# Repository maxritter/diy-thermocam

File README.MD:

# DIY-Thermocam

The DIY-Thermocam V3 is an open-source thermal imager based on the FLIR Lepton LWIR sensor.

Check out the official website for more information about the project: **[www.diy-thermocam.net](https://www.diy-thermocam.net/)**

**This repository contains:**

- **[Latest firmware releases](https://github.com/maxritter/diy-thermocam/releases)**
- **[Open-source firmware](https://github.com/maxritter/diy-thermocam/tree/master/firmware)**
- **[Desktop software](https://github.com/maxritter/diy-thermocam/tree/master/software)** 
- **[Device enclosure](https://github.com/maxritter/diy-thermocam/tree/master/enclosure)**
- **[Printed circuit board](https://github.com/maxritter/diy-thermocam/tree/master/pcb)**

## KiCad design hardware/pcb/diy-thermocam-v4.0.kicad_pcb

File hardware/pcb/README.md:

# DIY-Thermocam V4.0 PCB

The main board of the camera. A PCB manufacturer makes it and solders all parts on. You then plug in the Teensy 4.1, the FLIR Lepton on its Breakout Board V2.0, the display and the battery.

| Display side (top) | Module side (bottom) |
| --- | --- |
|  |  |

## Order the board

Choose a manufacturer and upload the three files from that manufacturer's folder in [`fab/`](fab/):

- the Gerber zip, `diy-thermocam-v4.0-bom.csv` and `diy-thermocam-v4.0-cpl.csv`

| Manufacturer | Folder | Good to know |
| --- | --- | --- |
| **[JLCPCB](https://jlcpcb.com/)** (recommended) | [`fab/jlcpcb/`](fab/jlcpcb/) | The Gerber zip is `diy-thermocam-v4.0-panel-gerbers.zip`: the board sits in its own routed break-off frame (see below). Every part comes from JLCPCB's own stock. The boost converter `U2` (`C2071784`) runs low at times; if the order shows a shortfall, pre-order it in the parts manager. Assembly starts at 2 boards. |
| [Seeed Fusion](https://www.seeedstudio.com/fusion_pcb.html) | [`fab/seeed/`](fab/seeed/) | Upload `diy-thermocam-v4.0-gerbers.zip`. Seeed buys the parts; the BOM links each one on LCSC. Also upload both assembly drawings. Takes about 4 weeks. |
| [PCBWay](https://www.pcbway.com/pcb-assembly.html) | [`fab/pcbway/`](fab/pcbway/) | Upload `diy-thermocam-v4.0-gerbers.zip`. PCBWay buys the parts; the notes column lists each LCSC number. Answer "no" to Chinese substitutes. |

**Board options:** 2 layers, 89.4 × 68.4 mm, 1.6 mm FR-4, 1 oz copper, lead-free HASL or ENIG, any solder mask colour.

**Assembly:** no soldering iron needed. Order double-sided assembly (Standard PCBA at JLCPCB), because the board has a part on its top side: all SMD parts and the Teensy and Lepton sockets go on the bottom side; only the display socket `J1` (2×20, through-hole) sits on the top side.

**Panel at JLCPCB.** Double-sided assembly needs a board of at least 70 × 70 mm. The JLCPCB Gerber already holds the board in a 107.4 × 86.4 mm routed frame with small break-off tabs, three tooling holes and six fiducials. The tabs stay clear of the USB-C connector, both switches and the tripod fin. In the order form:

- choose *Delivery Format: Panel by Customer*, 1 design, 1 × 1, and add no edge rails: the frame is in the file;
- in the assembly options set *Tooling holes: Added by Customer*, because the frame already has them;
- keep the CPL file as it is: its coordinates match the board inside the frame;
- turn on production-file confirmation, so you approve the placement before assembly starts;
- add the remark *"Seat the through-hole sockets (J1, J2, J5, J6) flush and square before soldering."*

Standard PCBA adds a setup fee, a stencil and a hand-soldering charge for the through-hole parts; the quote shows them before you pay. The boards arrive in their frames. Snap each one out by bending the frame, never the board, and never lever against the USB-C connector or the switches. File the small tab stubs flush.

**Before you confirm the production files,** compare the bottom placement with [`fab/diy-thermocam-v4.0-assembly-bottom.pdf`](fab/diy-thermocam-v4.0-assembly-bottom.pdf). The pin-1 marks of `U2`, `U3`, `U4`, `D1`, `D2`, `Q1` and `Q2` must line up. Rotations of bottom-side parts are the most common assembly mistake.

**Do not substitute** these parts; their heights, footprints or timing are part of the design:

- the spring pins `P1`–`P4`, the sockets `J1`, `J2`, `J5` and `J6`, the USB-C connector `J3` and the inductor `L1`.

## What you plug in

- **Teensy 4.1 with pins** into `J5`/`J6`, as it comes. Leave its five inner pads empty: spring pins `P3` (`VBAT`, clock supply) and `P4` (`Program`, PROG button) press on them from below. If pins are soldered there, cut them flush underneath first; never force the Teensy down.
- **FLIR Lepton 3.5** (or 3.1R or 2.5) snapped into a **FLIR Lepton Breakout Board V2.0 (`250-0577-00`, Rev R200)**, fitted onto a **Sullins `PPPC102LJBN-RC`** right-angle 2×10 female header (3.15 mm tails; do not substitute shorter-tail headers). Check the breakout label on arrival: older Rev R120 boards had D1 fitted backwards and cannot power from `J2` pin 2. Mount the breakout on four M2×18 screws with 12 mm sleeves plus three 0.3 mm M2 nylon washers (`003.03.010`) on each sleeve (= 12.9 mm spacing) and 1.2 mm ISO 4035 M2 thin nuts (`002.09.012`), so the right-angle header's bends clear `J2` even at worst-case socket height (+0.24 mm) while its legs seat 3.8 mm deep into `J2`.
- **BuyDisplay `ER-TFTM032-3`** into `J1`, from the display side.
- **LiPo battery** (Adafruit 258, or a `505060` cell; JST-PH) into `J4`. Check that its `+` wire matches the `+` mark first.

The full parts list with shops is in [`hardware/bom/`](../bom/README.md).

## What is on the board

| Function | How it works |
| --- | --- |
| USB-C | Charges the battery and carries USB data. Two spring pins (`P1`, `P2`) press on the USB pads under the Teensy, so the Teensy's own micro-USB port stays unused. Never plug a cable into it while the board is powered. |
| Charging | TI BQ24074 powers the camera over USB while charging the battery (about 0.45 A charge current via `R10 = 2.0 kΩ`, strictly under Adafruit 258's 500 mA limit; red `CHG` LED). Its USB input limit is 1.3 A nominal (up to 1.45 A worst case), so use a charger or port rated 1.5 A or more; a 500 mA hub port can cut out. |
| 5 V supply | TI TPS61022 boost converter. The slide switch `SW1` turns the camera off; the battery still charges while it is off. |
| Battery protection | `Q1`/`Q2` block a battery plugged in the wrong way round; `F1` is a 2 A resettable fuse. |
| Clock | An XC6206 regulator keeps the Teensy's clock running from the battery through spring pin `P3`, so no coin cell is needed. |
| Buttons | `SW2` capture button at the board edge; `SW3` PROG button behind a pinhole for firmware recovery, wired to the Teensy through spring pin `P4`. |
| Touch | Resistive touch works as delivered. A capacitive-touch display needs a soldering iron: cut `JP1`/`JP2` between pads 1–2, bridge pads 2–3, and close `JP3`. |

## First power-up

1. Main board only, battery connected, `SW1` on: 5.0 V (4.9–5.1 V) between `VIN` and `GND` on the Teensy socket. `SW1` off: 0 V.
2. Plug in USB-C: the red `CHG` LED lights while the battery charges.
3. With the Teensy plugged in, connect USB-C to a computer: the Teensy shows up as a USB device. This confirms `P1`/`P2` touch its USB pads.
4. Press PROG through the pinhole: Teensy Loader shows the Teensy in bootloader mode. This confirms `P4`.
5. Set the clock, switch off with `SW1` for a minute and on again: the time kept running. This confirms `P3`.
6. Plug in the FLIR Lepton Breakout Board V2.0 (with the Lepton snapped in) via the right-angle 2×10 female header into `J2`, switch on: the live thermal image appears.

## Change the design

The KiCad 10 project is [`diy-thermocam-v4.0`](diy-thermocam-v4.0.kicad_sch) with its symbol and footprint libraries ([`V40.kicad_sym`](V40.kicad_sym), [`V40.pretty/`](V40.pretty/), [`V40.3dshapes/`](V40.3dshapes/)). Part numbers live in [`hardware/bom/bom.csv`](../bom/bom.csv).

After a change, check the board and rebuild the order files:

```bash
kicad-cli sch erc --severity-error --exit-code-violations hardware/pcb/diy-thermocam-v4.0.kicad_sch
kicad-cli pcb drc --refill-zones --schematic-parity --severity-error --exit-code-violations hardware/pcb/diy-thermocam-v4.0.kicad_pcb
python3 hardware/pcb/scripts/export_fab.py
```

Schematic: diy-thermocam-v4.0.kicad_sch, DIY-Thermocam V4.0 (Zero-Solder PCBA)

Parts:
C1, C2, C3, C5, C10: 10uF; C_0805
C4, C8, C9: 22uF; C_0805
C6, C7, C11, C12: 100nF; C_0603
D1: USBLC6-2SC6; SOT23_6
D2: LED_Red_CHG; LED_0603
F1: PTC_2A_1206; FUSE_1206
H1, H2, H3, H4: M2.5_Hole; MountingHole_2.8mm_M2.5_Pad
J1: Display_2x20_Socket; PinSocket_2x20_Display
J2: Lepton_2x10_Socket; PinSocket_2x10_Lepton
J3: TYPE-C-31-M-12; USB_C_TYPE_C_31_M_12
J4: S2B-PH-SM4-TB; JST_PH_2P_RA
J5: Teensy_1x24_L; PinSocket_1x24
J6: Teensy_1x24_R; PinSocket_1x24
J8: I2C_EXT_DNP; I2C_PADS_1x04
JP1: CTP_SCL_SEL; SJ_3P_BRIDGED12
JP2: CTP_SDA_SEL; SJ_3P_BRIDGED12
JP3: CTP_INT_OPT; SJ_2P_OPEN
L1: 1.0uH_15A; L_0630
P1: Pogo_USB_DP; PogoPin_SMD_2.0mm
P2: Pogo_USB_DM; PogoPin_SMD_2.0mm
P3: Pogo_Teensy_VBAT; PogoPin_SMD_2.0mm
P4: Pogo_Teensy_PROG; PogoPin_SMD_2.0mm
Q1: AO3401A_RevPol; SOT23
Q2: AO3400A_RevPol_Ctl; SOT23
R1: 470k; R_0603
R2: 1M; R_0603
R3, R5, R15, R17, R24: 100k; R_0603
R4, R6: 4.7k; R_0603
R7, R8: 5.1k; R_0603
R9, R22: 10k; R_0603
R10: 2.0k; R_0603
R11: 1.2k; R_0603
R12: 1.0k; R_0603
R14, R20: 47k; R_0603
R16: 732k; R_0603
R18, R21: 750k; R_0603
R19: 10k_BL_PU; R_0603
R23: 3.0k; R_0603
SW1: JS102011SAQN; SW_SLIDE_RA
SW2: B3U-3000P; SW_TACT_RA
SW3: TS-1187A; SW_TACT_PROG
U2: TPS61022RWUT; TPS61022_VQFN7
U3: BQ24074RGTR; BQ24074_VQFN16
U4: XC6206P332MR_RTC; SOT23

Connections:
3V3: C7.1, J1.21, J5.15, J6.3, J8.2, R4.1, R6.1, R19.2, SW2.1
5V: C4.1, C5.1, C6.1, C9.1, J1.2, J2.2, J6.1, R16.1, U2.3
A16: J6.17, R3.2, R5.1
BOOST_EN: R15.1, SW1.2, U2.5
BOOST_FB: R16.2, R17.1, U2.4
BOOST_SW: L1.2, U2.2
BQ_CHG_N: D2.1, U3.9
BQ_EN2: R22.2, U3.5
BQ_ILIM: R11.1, U3.12
BQ_ISET: R10.1, U3.16
BQ_ITERM: R23.1, U3.15
BQ_TMR: R14.1, U3.14
BQ_TS: R9.1, U3.1
CTP_INT: J1.39, JP3.1
D2: J5.4, SW2.2
D3: J2.15, J5.5
D4: J5.6, JP3.2
D5: J5.7, JP2.1
D9: J5.11, JP1.1
D10: J1.25, J5.12
D11: J1.27, J1.34, J5.13
D12: J1.28, J1.32, J5.14
D13: J1.24, J1.33, J6.14
D18: J2.5, J6.9, J8.3, JP2.3, R4.2
D19: J2.8, J6.8, J8.4, JP1.3, R6.2
D21: J1.23, J6.6
D22: J1.29, J6.5, R19.1
D23: C12.1, J6.4, R1.2, R2.1
D26: J2.9, J5.18
D27: J2.7, J5.19
D38: J2.10, J6.19
D39: J2.12, J6.18
GND: C1.2, C2.2, C3.2, C4.2, C5.2, C6.2, C7.2, C8.2, C9.2, C10.2, C11.2, C12.2, D1.2, H1.1, H2.1, H3.1, H4.1, J1.1, J1.40, J2.1, J2.19, J3.A1, J3.A12, J3.B1, J3.B12, J3.SH, J4.2, J4.MP, J5.1, J6.2, J6.15, J8.1, Q2.2, R2.2, R5.2, R7.2, R8.2, R9.2, R10.2, R11.2, R14.2, R15.2, R17.2, R21.2, R23.2, SW1.1, SW3.1, U2.1, U2.6, U3.4, U3.6, U3.8, U3.17, U4.1
LCD_P30: J1.30, JP1.2
LCD_P31: J1.31, JP2.2
LED_CHG_A: D2.2, R12.2
LIPO_PROT: F1.1, Q1.2, R18.2, R24.1
LIPO_RAW: J4.1, Q1.3, R20.1, R24.2
Q1_GATE: Q1.1, Q2.3, R18.1
Q2_GATE: Q2.1, R20.2, R21.1
TEENSY_PROG: P4.1, SW3.2
USB_CC1: J3.A5, R7.1
USB_CC2: J3.B5, R8.1
USB_DM_RAW: D1.1, D1.6, J3.A7, J3.B7, P2.1
USB_DP_RAW: D1.3, D1.4, J3.A6, J3.B6, P1.1
VBAT: C10.1, P3.1, U4.2
VBUS: C1.1, D1.5, J3.A4, J3.A9, J3.B4, J3.B9, R3.1, R12.1, U3.13
VLIPO: C3.1, C11.1, F1.2, R1.1, U3.2, U3.3, U4.3
VSYS: C2.1, C8.1, L1.1, R22.1, SW1.3, U2.7, U3.10, U3.11

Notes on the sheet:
Switches, LEDs, JST-PH LiPo & Sensing
Teensy 4.1 Sockets + Zero-Solder USB Pogo Pins
3.2-inch Display & FLIR Lepton Sockets
TI TPS61022 5V Synchronous Boost + Decoupling
DIY-Thermocam V4.0 (Zero-Solder PCBA)
TI BQ24074 Power-Path Charger
USB-C + ESD

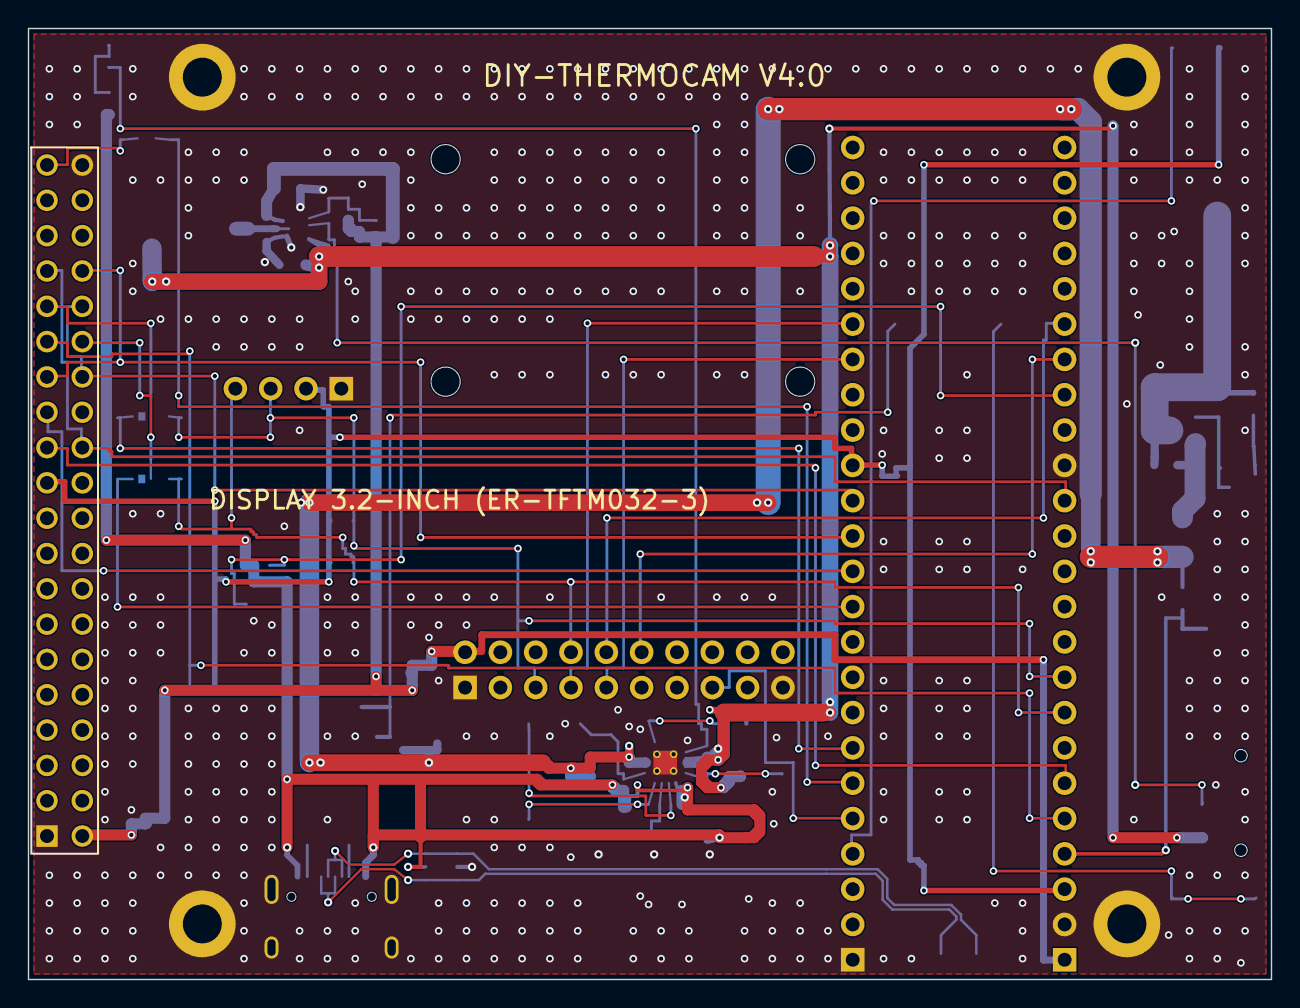
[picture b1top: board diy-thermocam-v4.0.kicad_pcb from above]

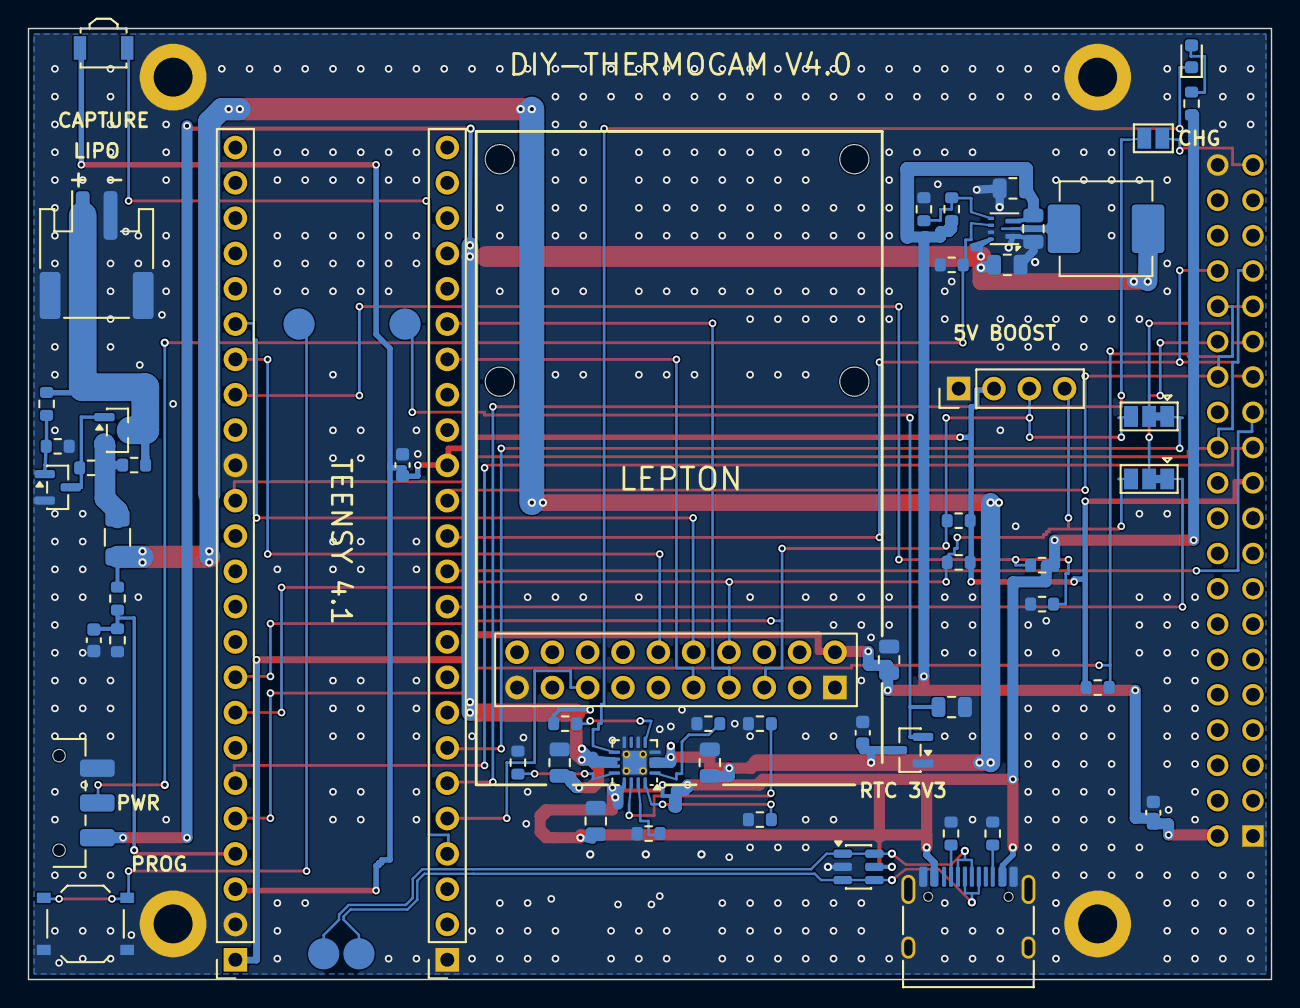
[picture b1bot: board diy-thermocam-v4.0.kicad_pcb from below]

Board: 2 copper layers, 89.4 x 68.4 mm, 69 parts (60 on the bottom side), 49 nets.

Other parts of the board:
H5, H6, H7, H8: M2_Lepton; MountingHole_2.1mm_M2

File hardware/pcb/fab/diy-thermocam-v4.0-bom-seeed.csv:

Designator,MPN,Qty,Seeed OPL,LCSC,Value,Footprint,Mount,PCBA Tier
"C1,C10,C2,C3,C5",CL21A106KAYNNNE,5,,C15850,10uF,C_0805,SMD,basic
"C11,C6,C7",CC0603KRX7R9BB104,3,,C14663,100nF,C_0603,SMD,basic
"C4,C8,C9",CL21A226MAQNNNE,3,,C45783,22uF,C_0805,SMD,basic
D1,USBLC6-2SC6,1,,C7519,USBLC6-2SC6,SOT23_6,SMD,extended
D2,KT-0603R,1,,C2286,LED_Red_CHG,LED_0603,SMD,basic
F1,SMD1206P200TF,1,,C20988,PTC_2A_1206,FUSE_1206,SMD,extended
J1,2.54-2*20,1,,C2977589,Display_2x20_Socket,PinSocket_2x20_Display,THT,extended
J2,DS1023-02-2x10SF11,1,,C18164970,Lepton_2x10_Socket,PinSocket_2x10_Lepton,THT,extended
J3,TYPE-C-31-M-12,1,,C165948,TYPE-C-31-M-12,USB_C_TYPE_C_31_M_12,SMD,extended
J4,S2B-PH-SM4-TB(LF)(SN),1,,C295747,S2B-PH-SM4-TB,JST_PH_2P_RA,SMD,extended
J5,HC-PM254-8.5H-1x24PZ,1,,C41376163,Teensy_1x24_L,PinSocket_1x24,THT,extended
J6,HC-PM254-8.5H-1x24PZ,1,,C41376163,Teensy_1x24_R,PinSocket_1x24,THT,extended
J7,2.54-1*5PFemale,1,,C50950,Teensy_1x05_Inner,PinSocket_1x05,THT,extended
L1,FXL0630-1R0-M,1,,C167216,1.0uH_15A,L_0630,SMD,extended
P1,YTC1P-8535-01,1,,C5221289,Pogo_USB_DP,PogoPin_SMD_2.0mm,SMD,extended
P2,YTC1P-8535-01,1,,C5221289,Pogo_USB_DM,PogoPin_SMD_2.0mm,SMD,extended
Q1,AO3401A,1,,C15127,AO3401A_RevPol,SOT23,SMD,basic
Q2,AO3400A,1,,C20917,AO3400A_RevPol_Ctl,SOT23,SMD,basic
"R1,R14,R20",0603WAF4702T5E,3,,C25819,47k,R_0603,SMD,basic
"R10,R12",0603WAF1001T5E,2,,C21190,1.0k,R_0603,SMD,basic
R11,0603WAF1201T5E,1,,C22765,1.2k,R_0603,SMD,basic
"R15,R17,R2,R3,R5",0603WAF1003T5E,5,,C25803,100k,R_0603,SMD,basic
"R16,R18,R21",0603WAF7503T5E,3,,C23240,750k,R_0603,SMD,extended
R19,0603WAF1002T5E,1,,C25804,10k_BL_PU,R_0603,SMD,basic
"R22,R9",0603WAF1002T5E,2,,C25804,10k,R_0603,SMD,basic
R23,0603WAF3001T5E,1,,C4211,3.0k,R_0603,SMD,basic
"R4,R6",0603WAF4701T5E,2,,C23162,4.7k,R_0603,SMD,basic
"R7,R8",0603WAF5101T5E,2,,C23186,5.1k,R_0603,SMD,basic
SW1,JS102011SAQN,1,,C221660,JS102011SAQN,SW_SLIDE_RA,SMD,extended
SW2,B3U-3000P,1,,C963349,B3U-3000P,SW_TACT_RA,SMD,extended
SW3,TS-1187A-B-A-B,1,,C318884,TS-1187A,SW_TACT_PROG,SMD,basic
U2,TPS61022RWUR,1,,C915088,TPS61022RWUR,TPS61022_VQFN7,SMD,extended
U3,BQ24074RGTR,1,,C54313,BQ24074RGTR,BQ24075_VQFN16,SMD,extended
U4,XC6206P332MR-G,1,,C5446,XC6206P332MR_RTC,SOT23,SMD,basic

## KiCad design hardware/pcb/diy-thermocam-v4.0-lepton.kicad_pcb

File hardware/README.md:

# DIY-Thermocam Hardware

PCB, enclosure, and Bill of Materials files for DIY-Thermocam, licensed under [CC BY-NC-SA 4.0](LICENSE): free to build and change for non-commercial use.

- **[PCB (`pcb/`)](pcb/README.md)** — KiCad 10 sources for the V4.0 main board (fully assembled by the fab), with Gerbers, BOM/CPL exports and 3D STEP models (`pcb/fab/`).
- **[Enclosure (`enclosure/`)](enclosure/README.md)** — Parametric [build123d](https://github.com/gumyr/build123d) CAD (`enclosure/cad/`), 3D-printed and laser-cut exports (`enclosure/exports/`), and Blender renders (`enclosure/renders/`).
- **[Bill of Materials (`bom/`)](bom/README.md)** — Single-source `bom.csv`, schema validator, and order guide.

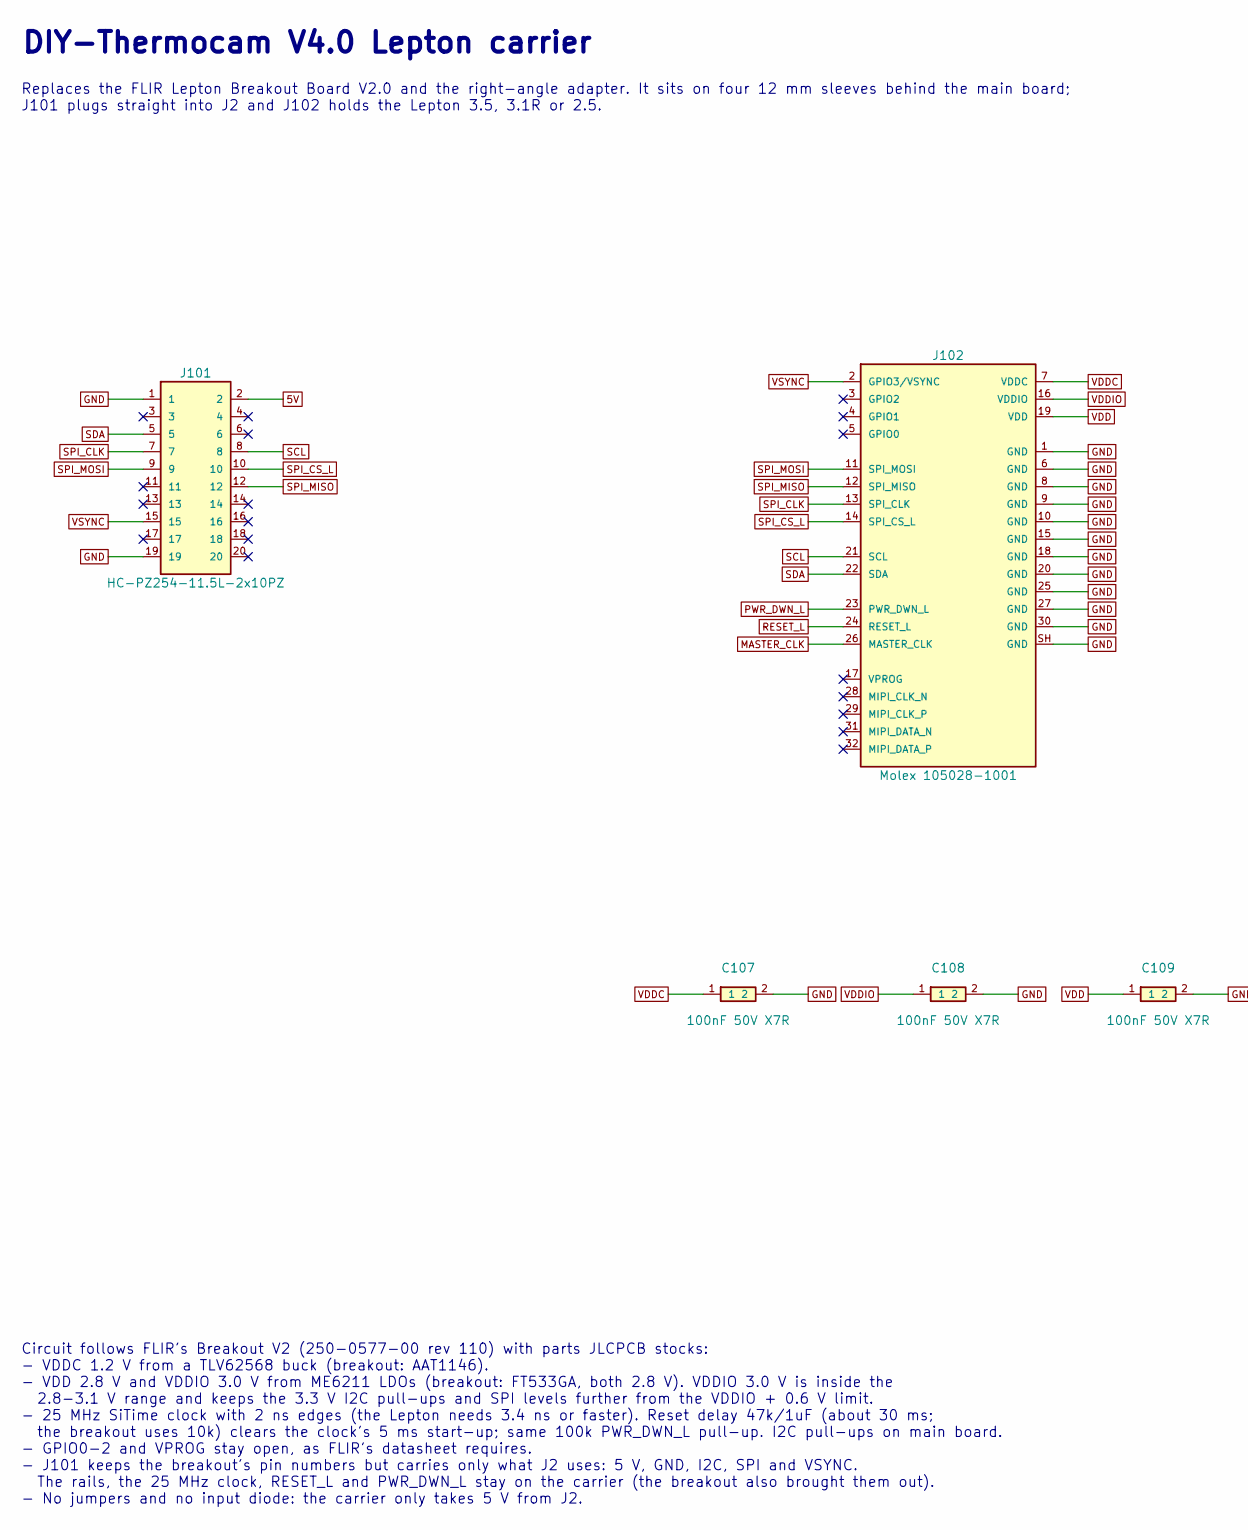
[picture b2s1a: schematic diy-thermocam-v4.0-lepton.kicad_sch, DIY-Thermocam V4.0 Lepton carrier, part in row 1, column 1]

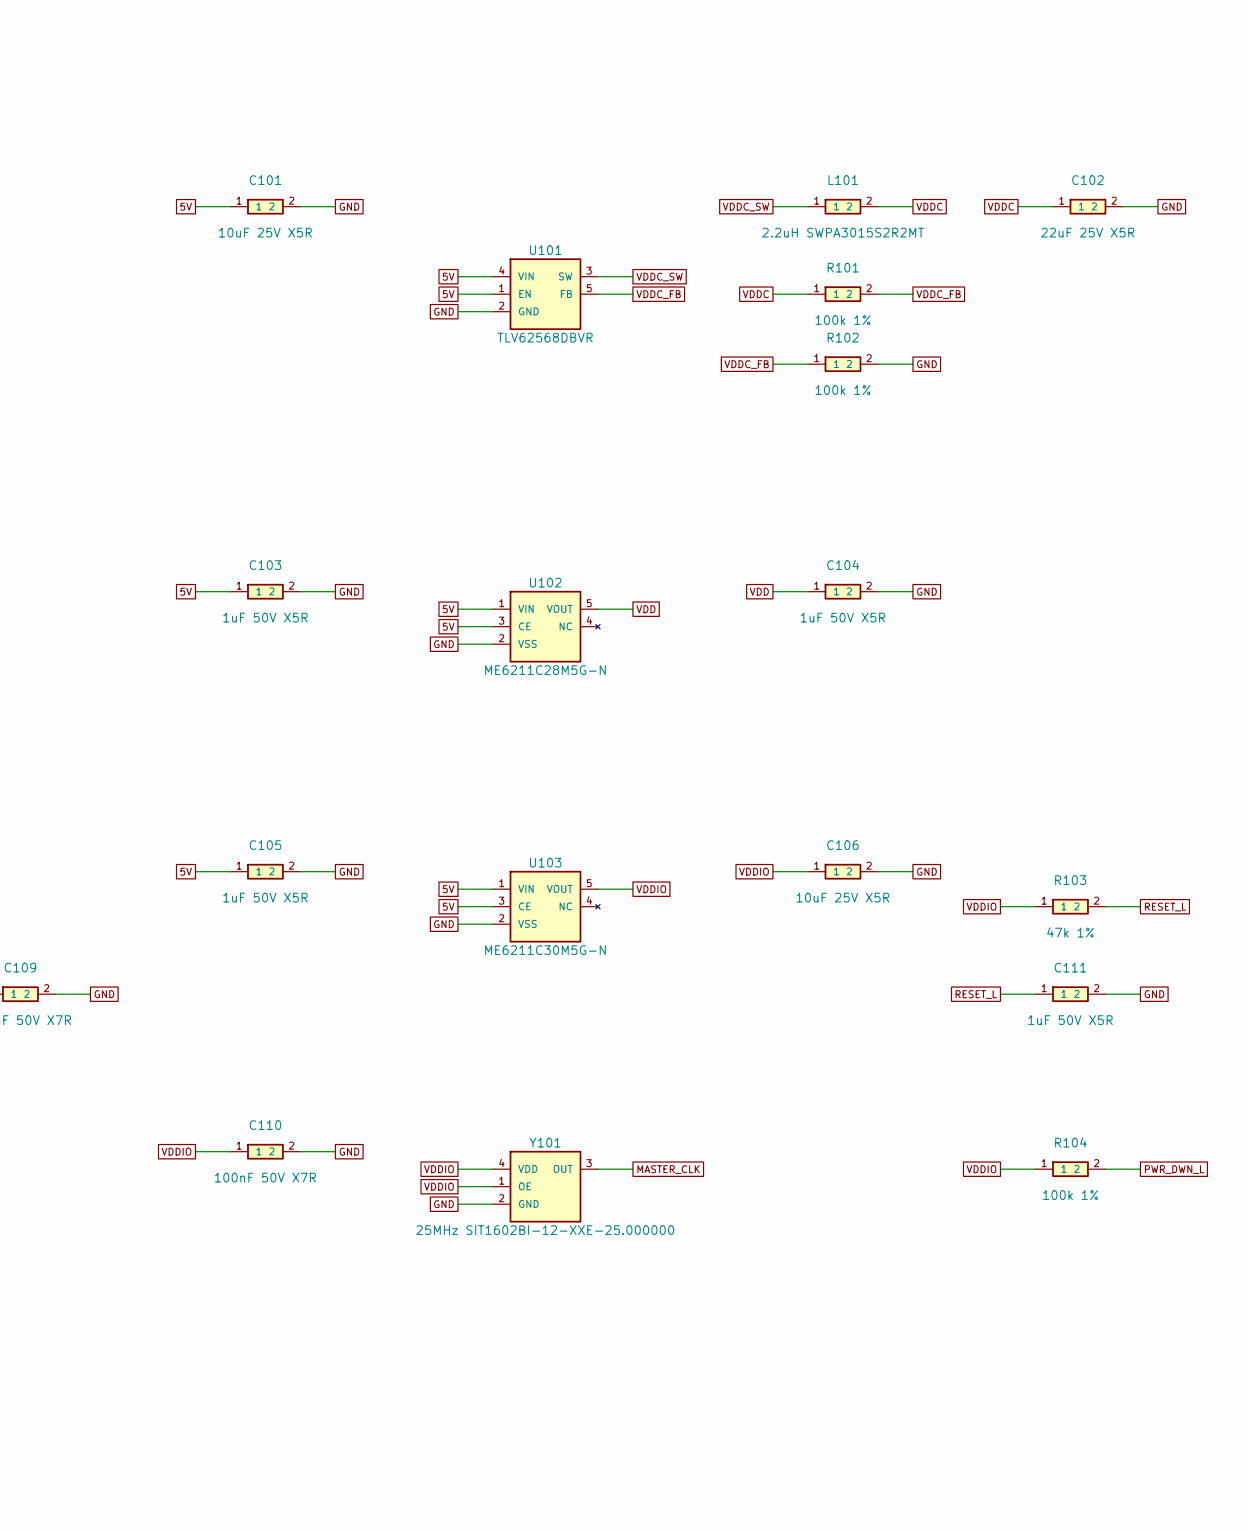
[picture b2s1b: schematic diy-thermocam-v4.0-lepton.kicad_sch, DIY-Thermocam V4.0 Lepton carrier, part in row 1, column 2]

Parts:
C101, C106: 10uF 25V X5R; C_0805
C102: 22uF 25V X5R; C_0805
C103, C104, C105, C111: 1uF 50V X5R; C_0603
C107, C108, C109, C110: 100nF 50V X7R; C_0603
J101: HC-PZ254-11.5L-2x10PZ; PinHeader_2x10_Carrier
J102: Molex 105028-1001; LeptonSocket_Molex_1050281001
L101: 2.2uH SWPA3015S2R2MT; L_SWPA3015
R101, R102, R104: 100k 1%; R_0603
R103: 47k 1%; R_0603
U101: TLV62568DBVR; SOT23_5
U102: ME6211C28M5G-N; SOT23_5
U103: ME6211C30M5G-N; SOT23_5
Y101: 25MHz SIT1602BI-12-XXE-25.000000; OSC_2520

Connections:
5V: C101.1, C103.1, C105.1, J101.2, U101.1 (EN), U101.4 (VIN), U102.1 (VIN), U102.3 (CE), U103.1 (VIN), U103.3 (CE)
GND: C101.2, C102.2, C103.2, C104.2, C105.2, C106.2, C107.2, C108.2, C109.2, C110.2, C111.2, J101.1, J101.19, J102.1 (GND), J102.6 (GND), J102.8 (GND), J102.9 (GND), J102.10 (GND), J102.15 (GND), J102.18 (GND), J102.20 (GND), J102.25 (GND), J102.27 (GND), J102.30 (GND), J102.SH (GND), R102.2, U101.2 (GND), U102.2 (VSS), U103.2 (VSS), Y101.2 (GND)
MASTER_CLK: J102.26 (MASTER_CLK), Y101.3 (OUT)
PWR_DWN_L: J102.23 (PWR_DWN_L), R104.2
RESET_L: C111.1, J102.24 (RESET_L), R103.2
SCL: J101.8, J102.21 (SCL)
SDA: J101.5, J102.22 (SDA)
SPI_CLK: J101.7, J102.13 (SPI_CLK)
SPI_CS_L: J101.10, J102.14 (SPI_CS_L)
SPI_MISO: J101.12, J102.12 (SPI_MISO)
SPI_MOSI: J101.9, J102.11 (SPI_MOSI)
VDD: C104.1, C109.1, J102.19 (VDD), U102.5 (VOUT)
VDDC: C102.1, C107.1, J102.7 (VDDC), L101.2, R101.1
VDDC_FB: R101.2, R102.1, U101.5 (FB)
VDDC_SW: L101.1, U101.3 (SW)
VDDIO: C106.1, C108.1, C110.1, J102.16 (VDDIO), R103.1, R104.1, U103.5 (VOUT), Y101.1 (OE), Y101.4 (VDD)
VSYNC: J101.15, J102.2 (GPIO3/VSYNC)

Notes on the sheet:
DIY-Thermocam V4.0 Lepton carrier
Replaces the FLIR Lepton Breakout Board V2.0 and the right-angle adapter. It sits on four 12 mm sleeves behind the main board; J101 plugs straight into J2 and J102 holds the Lepton 3.5, 3.1R or 2.5.
Circuit follows FLIR's Breakout V2 (250-0577-00 rev 110) with parts JLCPCB stocks: - VDDC 1.2 V from a TLV62568 buck (breakout: AAT1146). - VDD 2.8 V and VDDIO 3.0 V from ME6211 LDOs (breakout: FT533GA, both 2.8 V). VDDIO 3.0 V is inside the 2.8-3.1 V range and keeps the 3.3 V I2C pull-ups and SPI 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

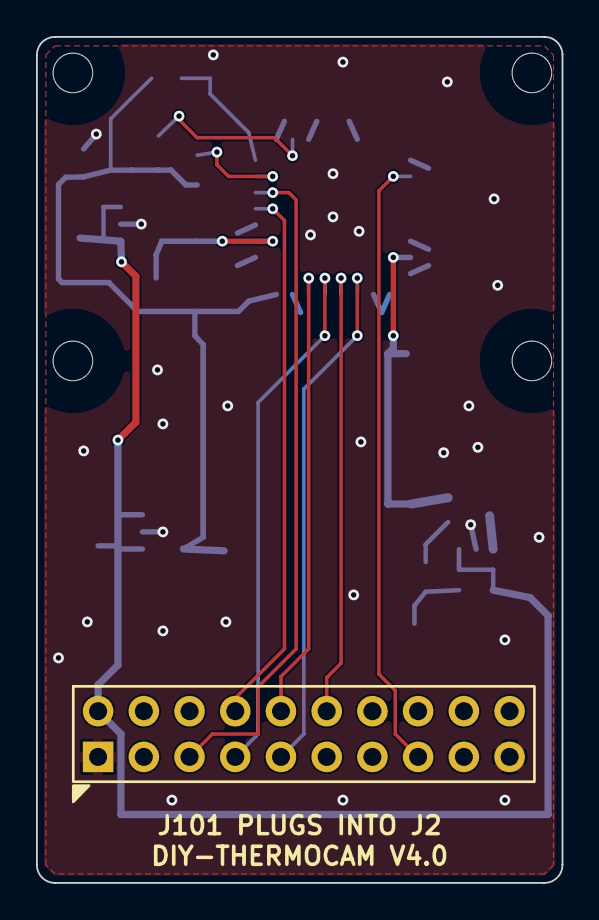
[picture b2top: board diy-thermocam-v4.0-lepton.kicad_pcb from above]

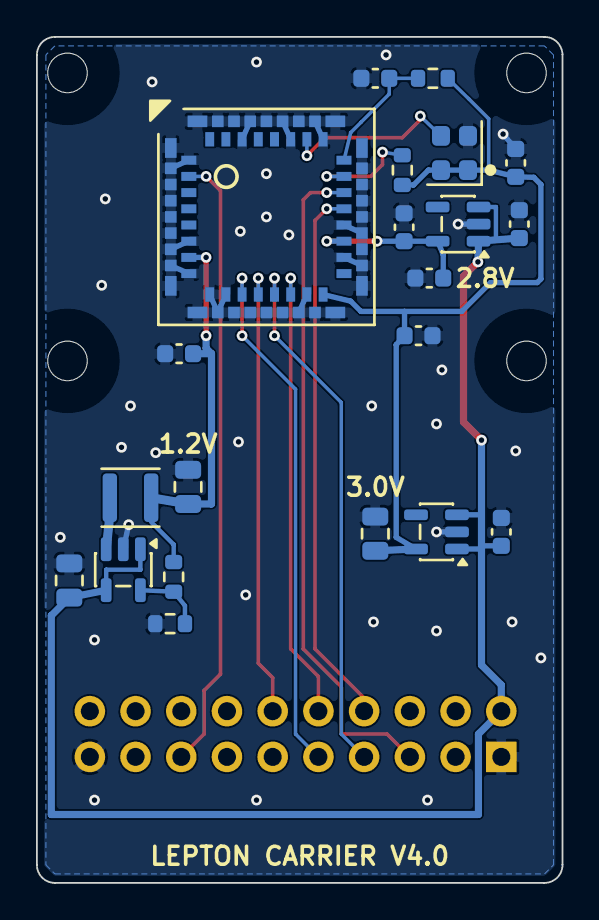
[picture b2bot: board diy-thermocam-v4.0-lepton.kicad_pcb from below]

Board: 2 copper layers, 29.2 x 47.0 mm, 26 parts (21 on the bottom side), 17 nets.

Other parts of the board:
H101, H102, H103, H104: M2; MountingHole_2.2mm_M2_NPTH

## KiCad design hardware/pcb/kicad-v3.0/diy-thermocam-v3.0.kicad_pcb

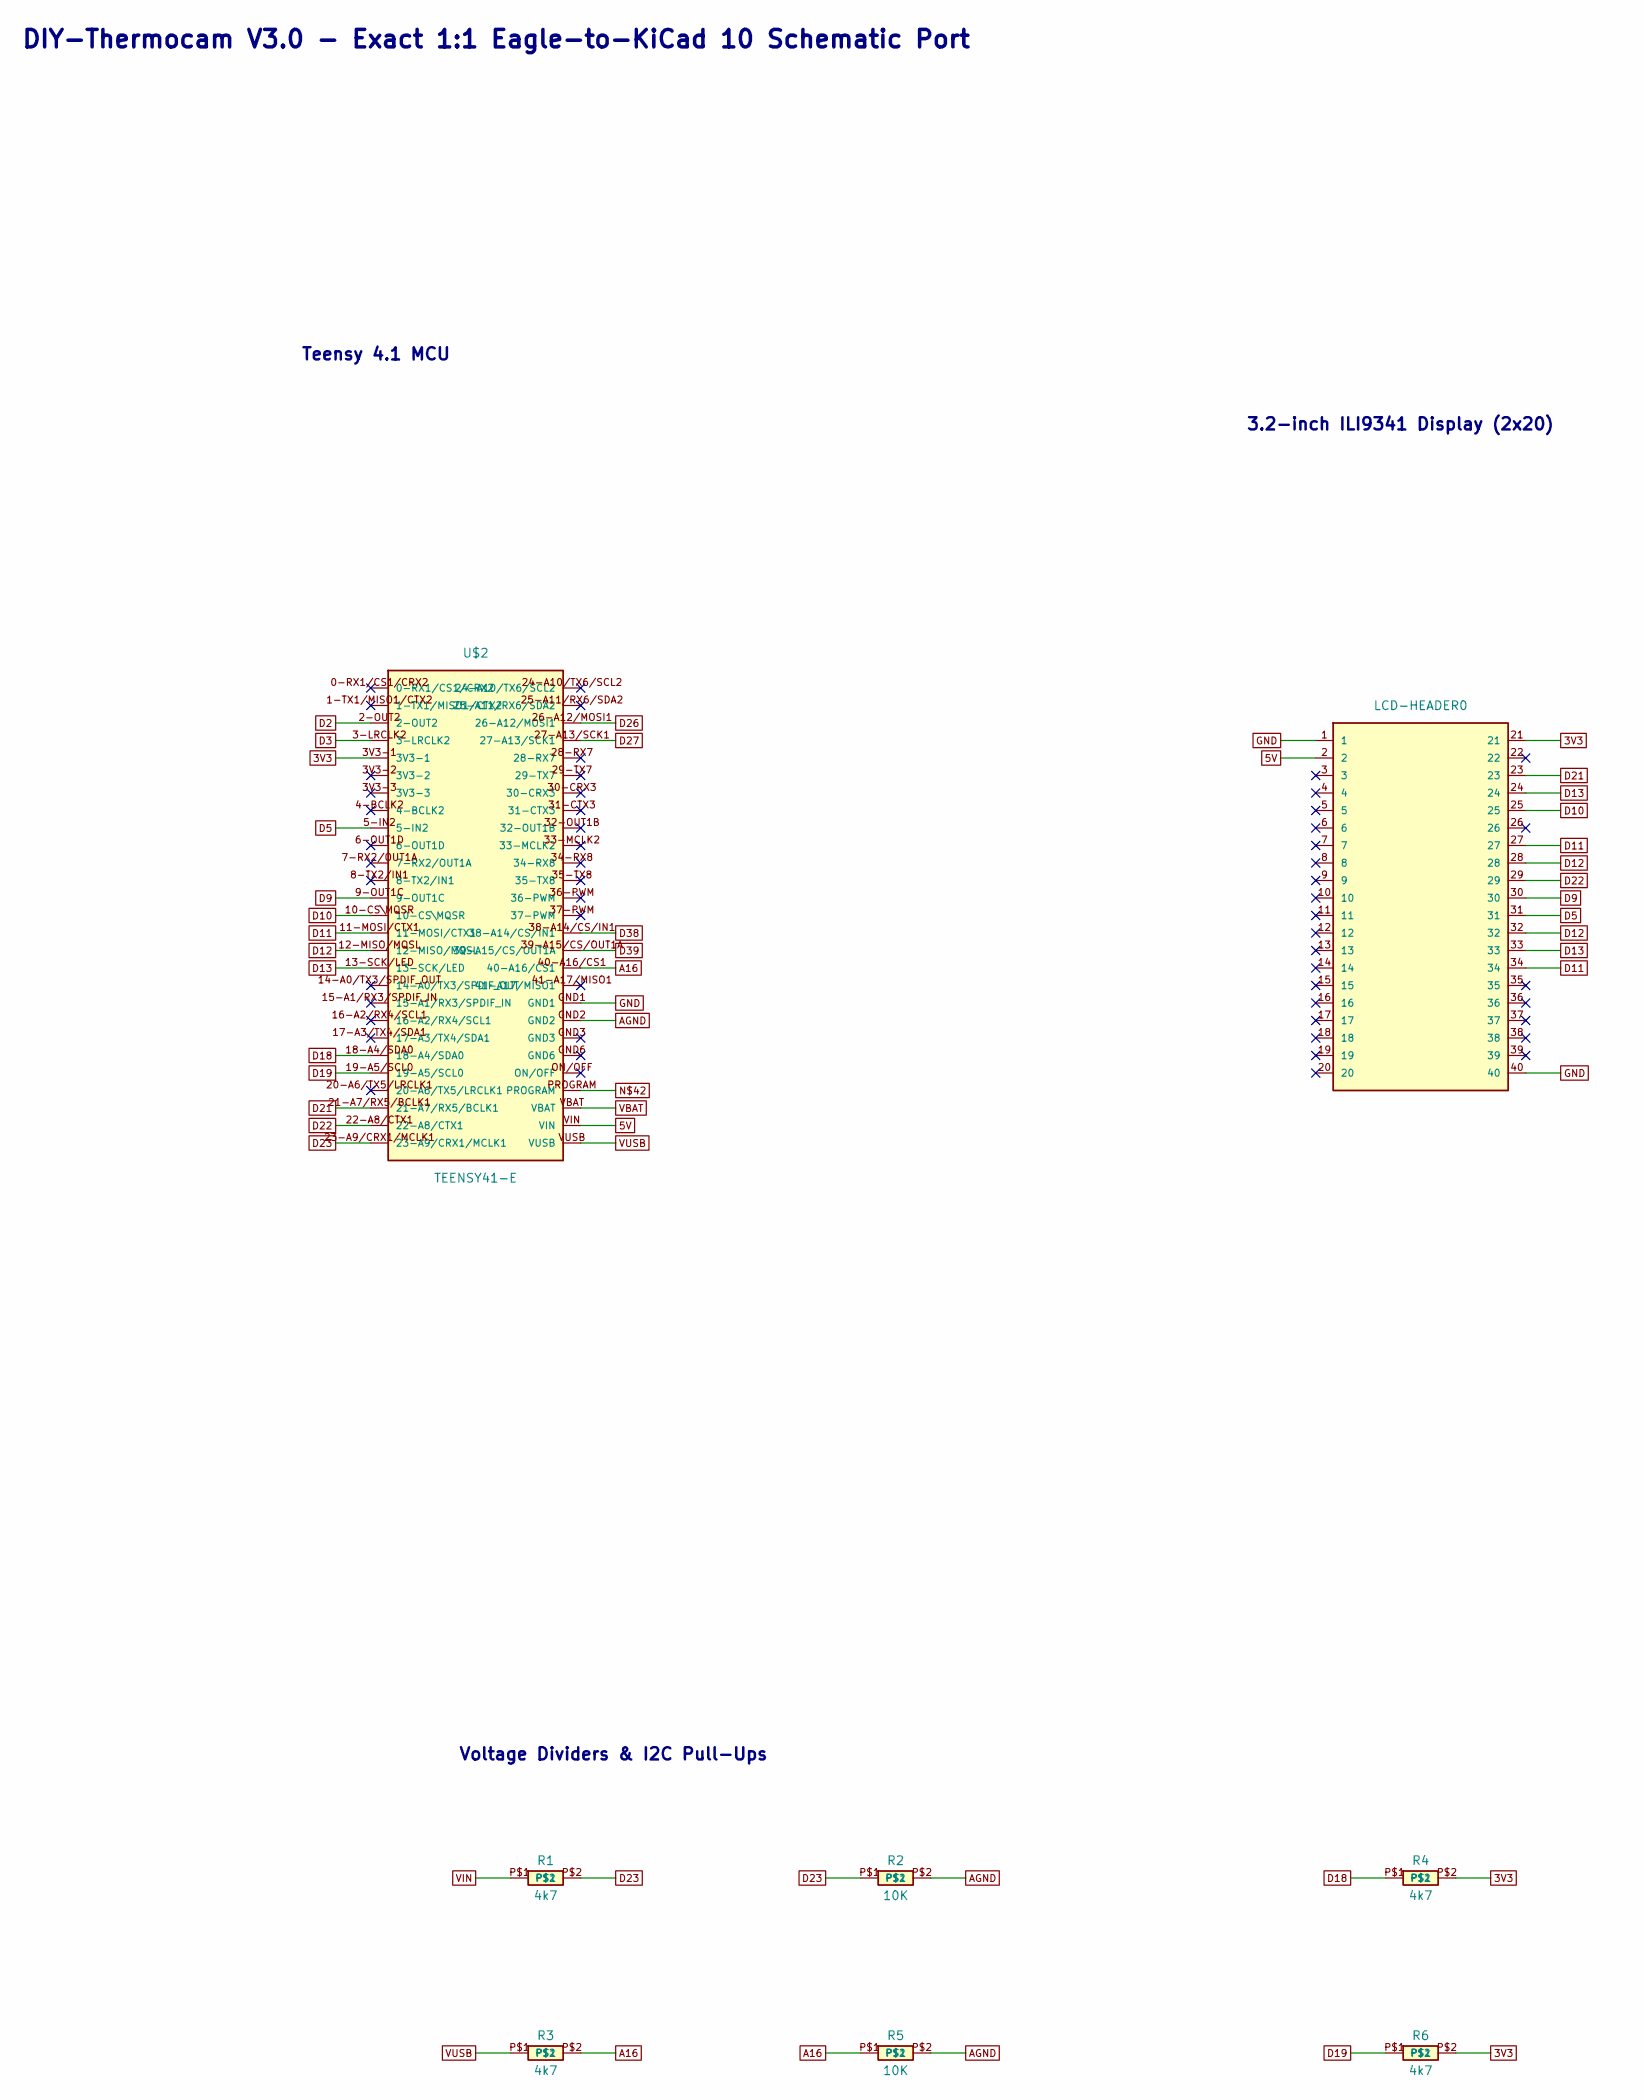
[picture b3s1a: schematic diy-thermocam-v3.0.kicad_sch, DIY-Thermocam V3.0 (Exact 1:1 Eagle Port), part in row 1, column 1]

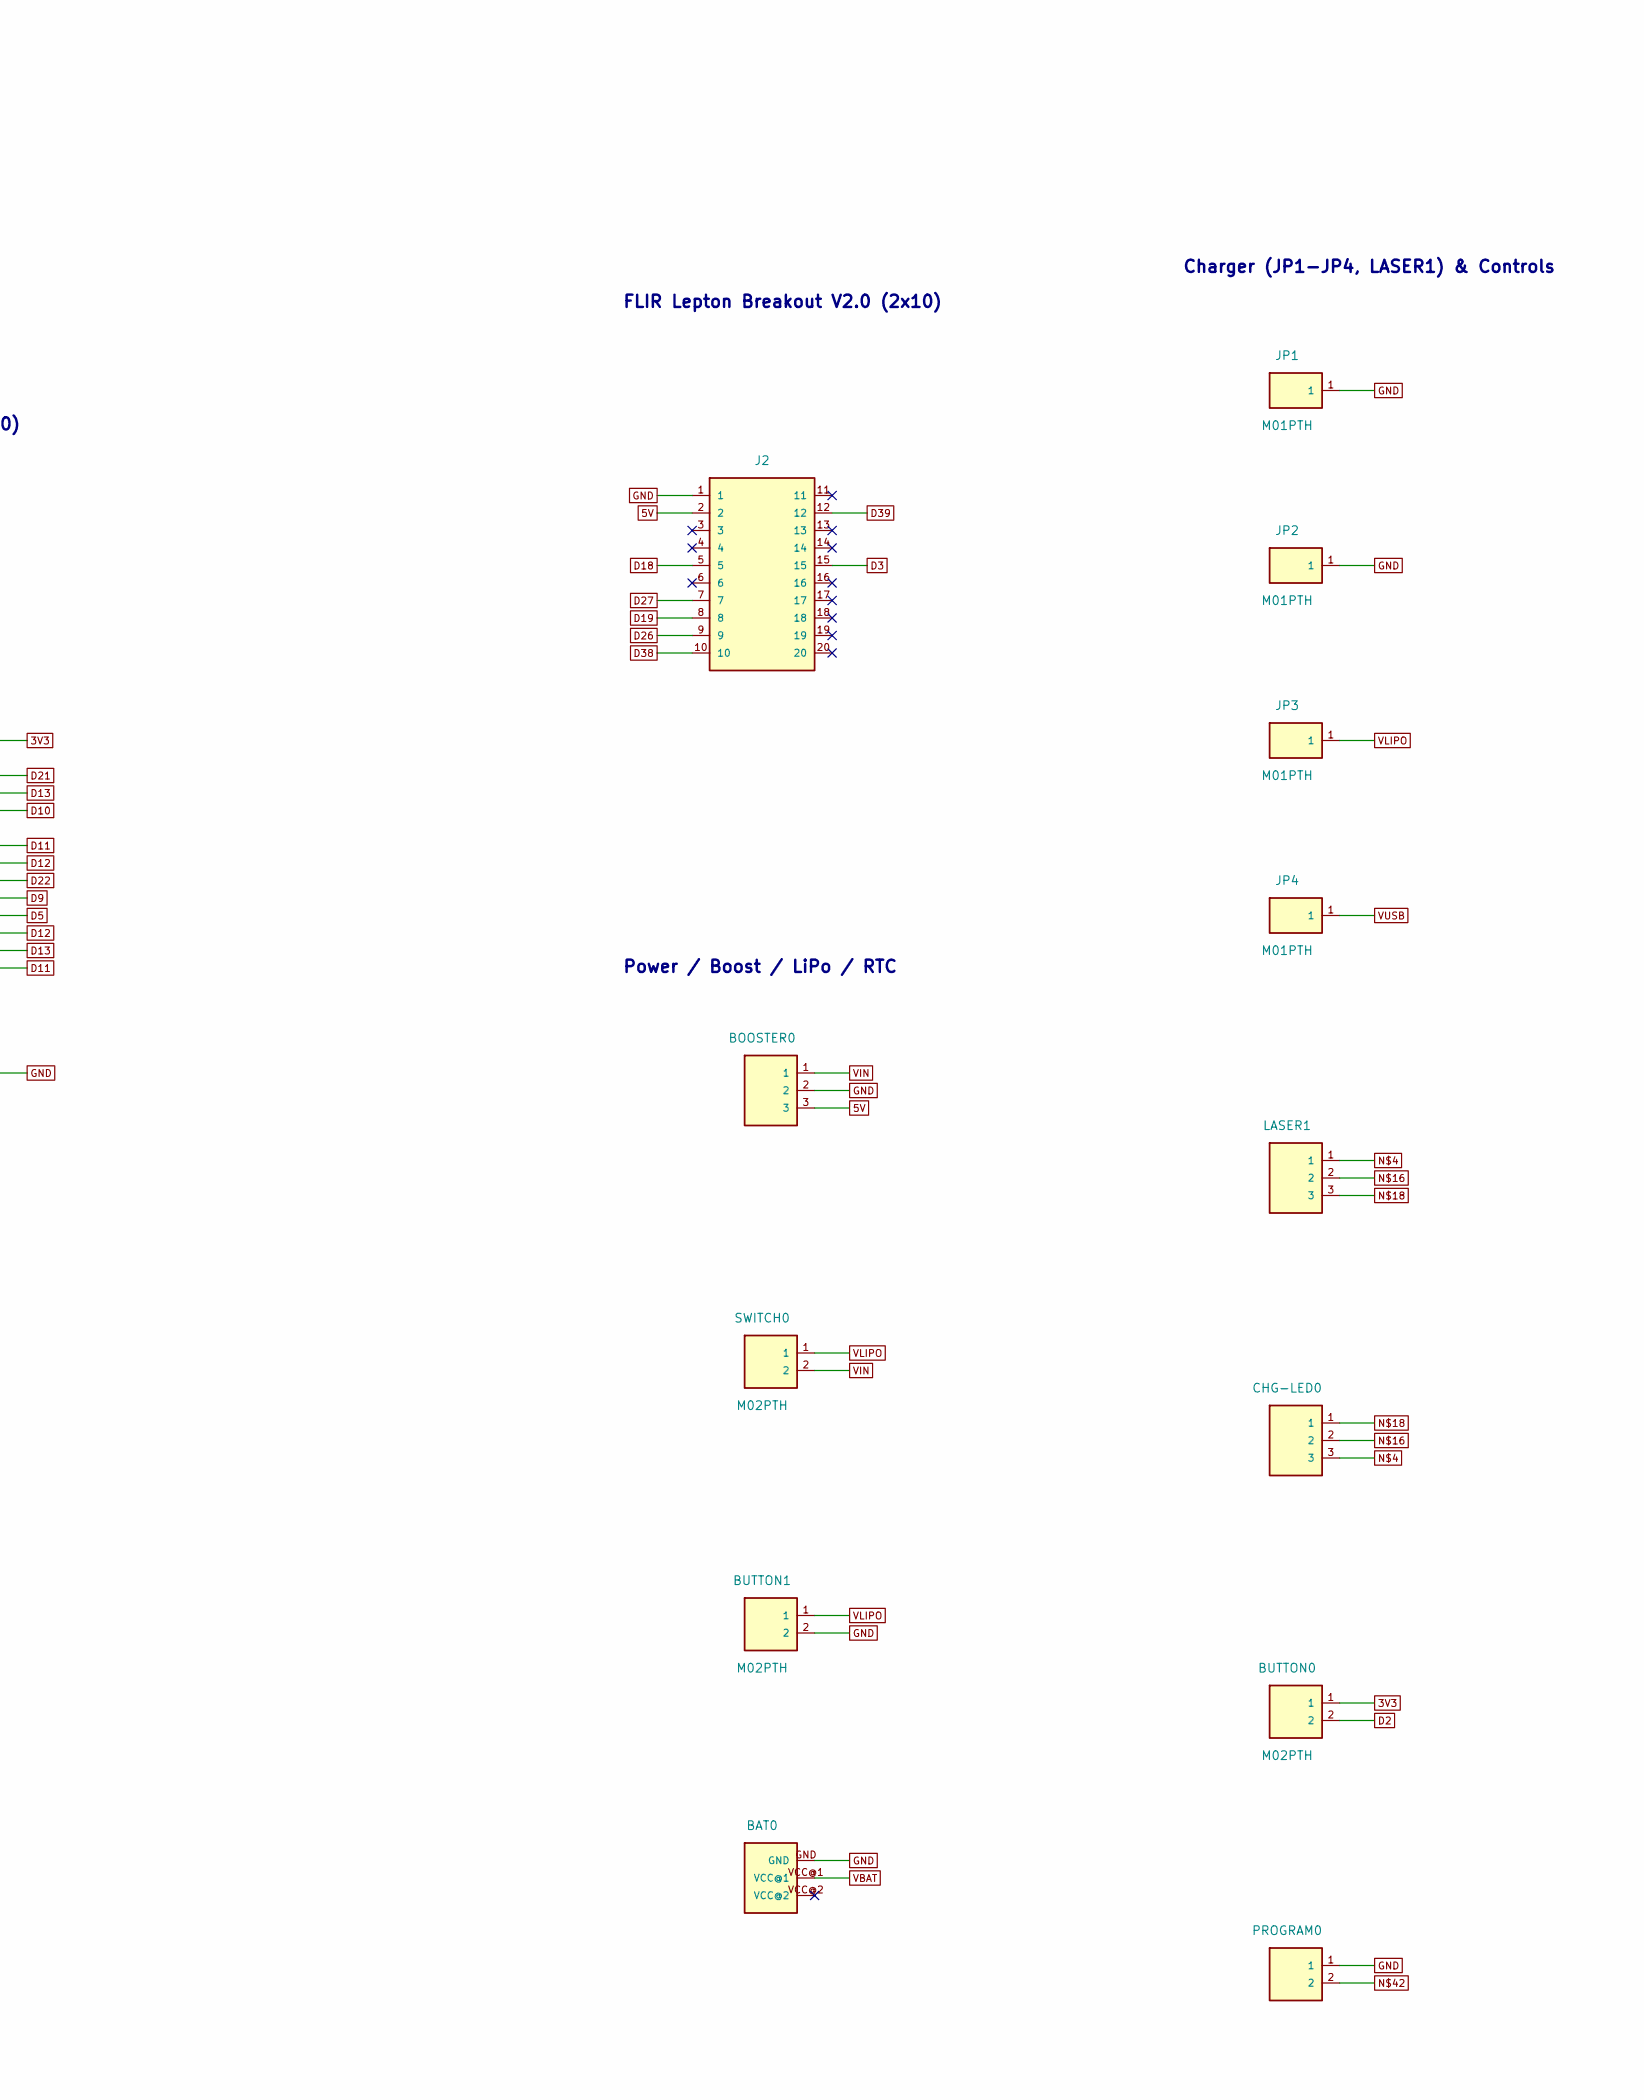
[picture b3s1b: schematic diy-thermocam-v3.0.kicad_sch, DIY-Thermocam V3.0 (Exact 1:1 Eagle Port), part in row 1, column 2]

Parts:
BAT0: BATTCON_12MM_PTH
BOOSTER0: 1X03
BUTTON0, BUTTON1: M02PTH; 1X02
CHG-LED0: 1X03
J2: 2X10_NOSILK
JP1, JP2, JP3, JP4: M01PTH; 1X01
LASER1: 1X03
LCD-HEADER0: 2X20
PROGRAM0: SJ
R1, R3, R4, R6: 4k7; AXIAL-0.4
R2, R5: 10K; AXIAL-0.4
SWITCH0: M02PTH; 1X02
U$2: TEENSY41-E; TENNSY41-E

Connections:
3V3: BUTTON0.1, LCD-HEADER0.21, R4.P$2, R6.P$2, U$2.3V3-1
5V: BOOSTER0.3, J2.2, LCD-HEADER0.2, U$2.VIN
A16: R3.P$2, R5.P$1, U$2.40-A16/CS1
AGND: R2.P$2, R5.P$2, U$2.GND2
D2: BUTTON0.2, U$2.2-OUT2
D3: J2.15, U$2.3-LRCLK2
D5: LCD-HEADER0.31, U$2.5-IN2
D9: LCD-HEADER0.30, U$2.9-OUT1C
D10: LCD-HEADER0.25, U$2.10-CS\MQSR
D11: LCD-HEADER0.27, LCD-HEADER0.34, U$2.11-MOSI/CTX1
D12: LCD-HEADER0.28, LCD-HEADER0.32, U$2.12-MISO/MQSL
D13: LCD-HEADER0.24, LCD-HEADER0.33, U$2.13-SCK/LED
D18: J2.5, R4.P$1, U$2.18-A4/SDA0
D19: J2.8, R6.P$1, U$2.19-A5/SCL0
D21: LCD-HEADER0.23, U$2.21-A7/RX5/BCLK1
D22: LCD-HEADER0.29, U$2.22-A8/CTX1
D23: R1.P$2, R2.P$1, U$2.23-A9/CRX1/MCLK1
D26: J2.9, U$2.26-A12/MOSI1
D27: J2.7, U$2.27-A13/SCK1
D38: J2.10, U$2.38-A14/CS/IN1
D39: J2.12, U$2.39-A15/CS/OUT1A
GND: BAT0.GND, BOOSTER0.2, BUTTON1.2, J2.1, JP1.1, JP2.1, LCD-HEADER0.1, LCD-HEADER0.40, PROGRAM0.1, U$2.GND1
unnamed: CHG-LED0.3, LASER1.1
unnamed: CHG-LED0.2, LASER1.2
unnamed: CHG-LED0.1, LASER1.3
unnamed: PROGRAM0.2, U$2.PROGRAM
VBAT: BAT0.VCC@1, U$2.VBAT
VIN: BOOSTER0.1, R1.P$1, SWITCH0.2
VLIPO: BUTTON1.1, JP3.1, SWITCH0.1
VUSB: JP4.1, R3.P$1, U$2.VUSB

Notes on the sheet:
Teensy 4.1 MCU
FLIR Lepton Breakout V2.0 (2x10)
Voltage Dividers & I2C Pull-Ups
DIY-Thermocam V3.0 - Exact 1:1 Eagle-to-KiCad 10 Schematic Port
Charger (JP1-JP4, LASER1) & Controls
3.2-inch ILI9341 Display (2x20)
Power / Boost / LiPo / RTC

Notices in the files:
hardware/pcb/diy-thermocam-v4.0-lepton.kicad_sch:
DIY-Thermocam (GPL-3.0)
hardware/pcb/diy-thermocam-v4.0.kicad_sch:
DIY-Thermocam (CC BY-NC-SA 4.0)
